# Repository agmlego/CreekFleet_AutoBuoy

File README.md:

# CreekFleet AutoBuoy

Autonomous mark buoys à la [MarkSetBot](https://www.marksetbot.com/), but DIY and (hopefully) lower-cost.

I am not affiliated with nor do I represent the MarkSetBot group. I just thought their concept was neat, but my fleet does not have the capital to buy into it.

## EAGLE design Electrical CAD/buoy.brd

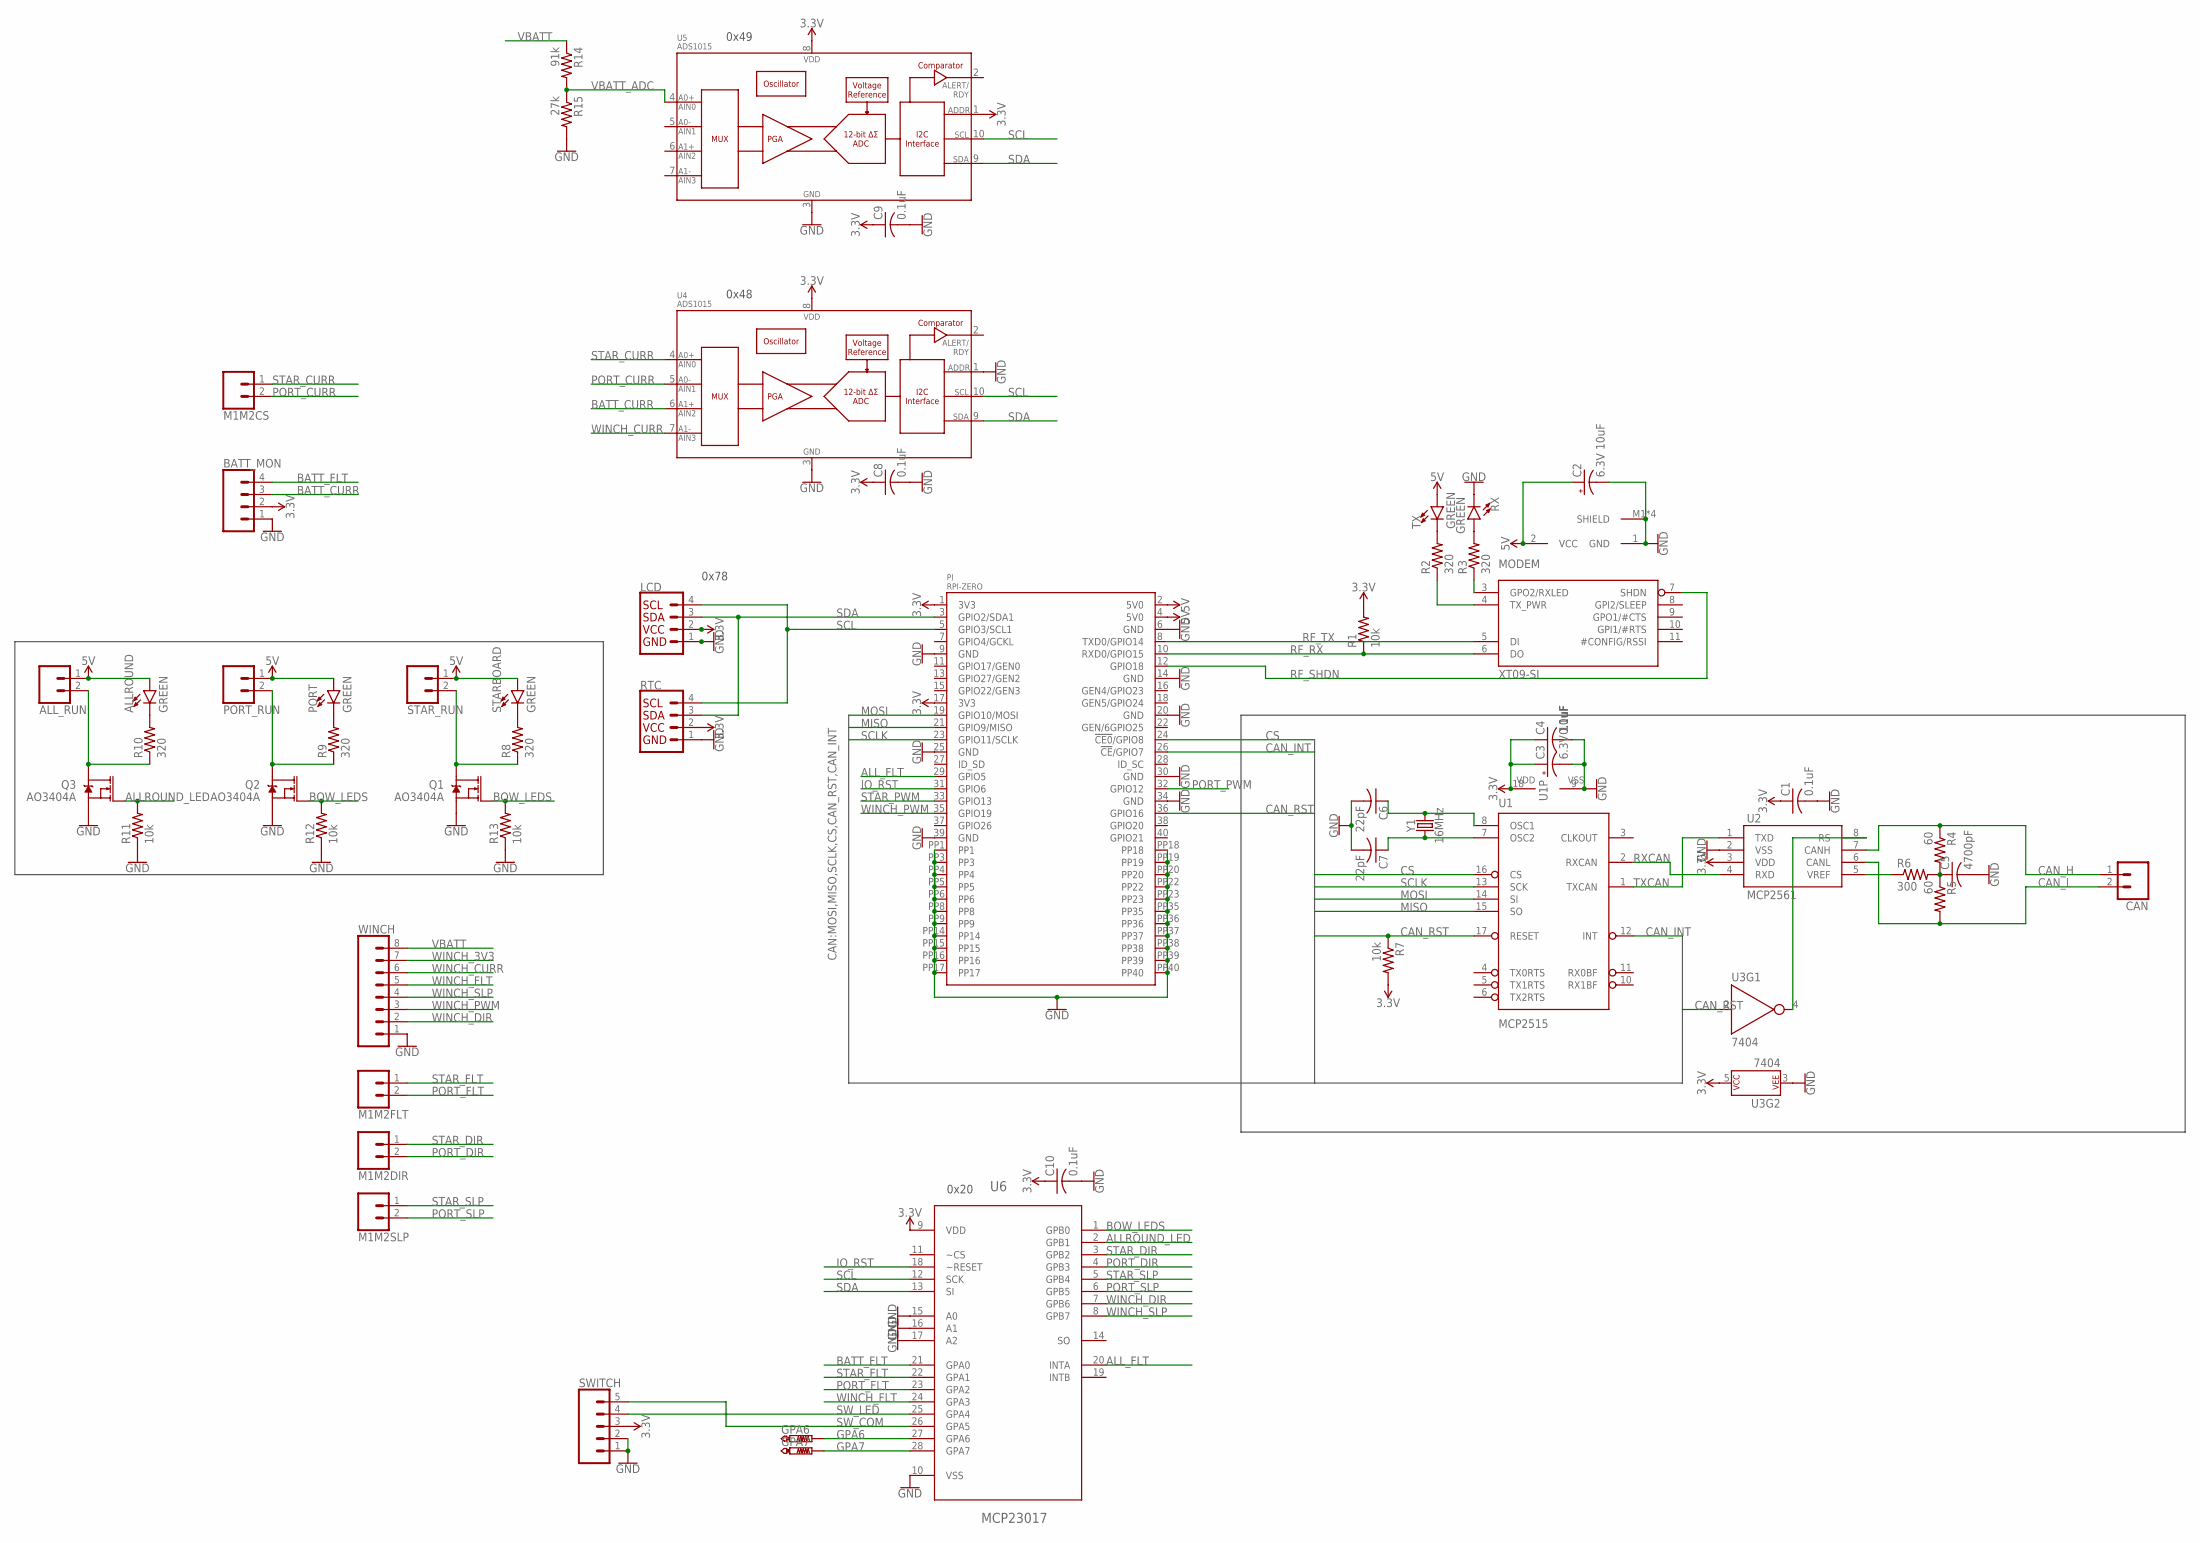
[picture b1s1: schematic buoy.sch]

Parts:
ALLROUND: GREEN; LED-1206
ALL_RUN: CONN_02JST-PTH-2; JST-2-PTH
BATT_MON: CONN_04LOCK; 1X04_LOCK
C1, C4, C8, C9, C10: 0.1uF; C1206
C2, C3: 6.3V 10uF; 153CLV-0405
C5: 4700pF; C1206
C6, C7: 22pF; C1206
CAN: CONN_02JST-PTH-2; JST-2-PTH
GPA6, GPA7: PTR1B1,27; B1,27
LCD: I2C_STANDARD; 1X04
M1M2CS, M1M2DIR, M1M2FLT, M1M2SLP: CONN_02JST-PTH-2; JST-2-PTH
MODEM: XT09-SI
PI: RPI-ZERO; RASP_PI_ZERO_BOARD_FULL
PORT: GREEN; LED-1206
PORT_RUN: CONN_02JST-PTH-2; JST-2-PTH
Q1, Q2, Q3: AO3404A; SOT23-3
R1, R7, R11, R12, R13: 10k; R1206
R2, R3, R8, R9, R10: 320; R1206
R4, R5: 60; R1206
R6: 300; R1206
R14: 91k; R1206
R15: 27k; R1206
RTC: I2C_STANDARD; 1X04
RX: GREEN; LED-1206
STARBOARD: GREEN; LED-1206
STAR_RUN: CONN_02JST-PTH-2; JST-2-PTH
SWITCH: CONN_05LOCK; 1X05_LOCK
TX: GREEN; LED-1206
U1: MCP2515; SO18W
U2: MCP2561; SO08
U3: 7404; SOT353
U4, U5: ADS1015; MSOP10
U6: MCP23017; SOIC127P030X265-28N
WINCH: CONN_08LOCK; 1X08_LOCK
Y1: 16MHz; HC49US

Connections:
3.3V: BATT_MON.2, C1.1, C3.+, C4.1, C8.1, C9.1, C10.1, LCD.2, PI.1 (3V3), PI.17 (3V3), R1.2, R7.2, RTC.2, SWITCH.3, U1.18 (VDD), U2.3 (VDD), U3.5 (P$V+), U4.8 (VDD), U5.1 (ADDR), U5.8 (VDD), U6.9 (VDD)
5V: ALLROUND.A, ALL_RUN.1, C2.+, MODEM.2 (VCC), PI.2 (5V0), PI.4 (5V0), PORT.A, PORT_RUN.1, STARBOARD.A, STAR_RUN.1, TX.A
#CAN_RST: U2.8 (RS), U3.4 (Y)
ALLROUND_IND: ALLROUND.C, R10.2
ALLROUND_LED: Q3.1 (G), R11.2, U6.2 (GPB1)
ALLROUND_LED_LSD: ALL_RUN.2, Q3.3 (D), R10.1
ALL_FLT: PI.29 (GPIO5), U6.20 (INTA)
BATT_CURR: BATT_MON.3, U4.6 (AIN2)
BATT_FLT: BATT_MON.4, U6.21 (GPA0)
BOW_LEDS: Q1.1 (G), Q2.1 (G), R12.2, R13.2, U6.1 (GPB0)
CAN_H: CAN.1, R4.1, U2.7 (CANH)
CAN_INT: PI.26 (!CE!/GPIO7), U1.12 (INT)
CAN_L: CAN.2, R5.2, U2.6 (CANL)
CAN_RST: PI.36 (GPIO16), R7.1, U1.17 (RESET), U3.2 (A)
CAN_TERM: C5.1, R4.2, R5.1, R6.2
CAN_VREF: R6.1, U2.5 (VREF)
CS: PI.24 (!CE0!/GPIO8), U1.16 (CS)
GND: BATT_MON.1, C1.2, C2.-, C3.-, C4.2, C5.2, C6.2, C7.2, C8.2, C9.2, C10.2, LCD.1, MODEM.1 (GND), MODEM.M1 (SHIELD), MODEM.M2 (SHIELD), MODEM.M3 (SHIELD), MODEM.M4 (SHIELD), PI.6 (GND), PI.9 (GND), PI.14 (GND), PI.20 (GND), PI.25 (GND), PI.30 (GND), PI.34 (GND), PI.39 (GND), PI.PP1, PI.PP3, PI.PP4, PI.PP5, PI.PP6, PI.PP8, PI.PP9, PI.PP14, PI.PP15, PI.PP16, PI.PP17, PI.PP18, PI.PP19, PI.PP20, PI.PP22, PI.PP23, PI.PP35, PI.PP36, PI.PP37, PI.PP38, PI.PP39, PI.PP40, Q1.2 (S), Q2.2 (S), Q3.2 (S), R11.1, R12.1, R13.1, R15.2, RTC.1, RX.C, SWITCH.1, SWITCH.2, U1.9 (VSS), U2.2 (VSS), U3.3 (P$V-), U4.1 (ADDR), U4.3 (VSS), U5.3 (VSS), U6.10 (VSS), U6.15 (A0), U6.16 (A1), U6.17 (A2), WINCH.1
GPA6: GPA6.TP, U6.27 (GPA6)
GPA7: GPA7.TP, U6.28 (GPA7)
IO_RST: PI.31 (GPIO6), U6.18 (~RESET)
MISO: PI.21 (GPIO9/MISO), U1.15 (SO)
MOSI: PI.19 (GPIO10/MOSI), U1.14 (SI)
OSC1: C6.1, U1.8 (OSC1), Y1.2
OSC2: C7.1, U1.7 (OSC2), Y1.1
PORT_CURR: M1M2CS.2, U4.5 (AIN1)
PORT_DIR: M1M2DIR.2, U6.4 (GPB3)
PORT_FLT: M1M2FLT.2, U6.23 (GPA2)
PORT_IND: PORT.C, R9.2
PORT_LED_LSD: PORT_RUN.2, Q2.3 (D), R9.1
PORT_PWM: PI.32 (GPIO12)
PORT_SLP: M1M2SLP.2, U6.6 (GPB5)
RF_RX: MODEM.6 (DO), PI.10 (RXD0/GPIO15), R1.1
RF_SHDN: MODEM.7 (SHDN), PI.12 (GPIO18)
RF_TX: MODEM.5 (DI), PI.8 (TXD0/GPIO14)
RXCAN: U1.2 (RXCAN), U2.4 (RXD)
RXLED: MODEM.3 (GPO2/RXLED), R3.1
RXLED_L: R3.2, RX.A
SCL: LCD.4, PI.5 (GPIO3/SCL1), RTC.4, U4.10 (SCL), U5.10 (SCL), U6.12 (SCK)
SCLK: PI.23 (GPIO11/SCLK), U1.13 (SCK)
SDA: LCD.3, PI.3 (GPIO2/SDA1), RTC.3, U4.9 (SDA), U5.9 (SDA), U6.13 (SI)
STARBOARD_LED_LSD: Q1.3 (D), R8.1, STAR_RUN.2
STAR_CURR: M1M2CS.1, U4.4 (AIN0)
STAR_DIR: M1M2DIR.1, U6.3 (GPB2)
STAR_FLT: M1M2FLT.1, U6.22 (GPA1)
STAR_IND: R8.2, STARBOARD.C
STAR_PWM: PI.33 (GPIO13)
STAR_SLP: M1M2SLP.1, U6.5 (GPB4)
SW_COM: SWITCH.5, U6.26 (GPA5)
SW_LED: SWITCH.4, U6.25 (GPA4)
TXCAN: U1.1 (TXCAN), U2.1 (TXD)
TX_PWR: MODEM.4 (TX_PWR), R2.1
TX_PWR_L: R2.2, TX.C
VBATT: R14.1, WINCH.8
VBATT_ADC: R14.2, R15.1, U5.4 (AIN0)
WINCH_3V3: WINCH.7
WINCH_CURR: U4.7 (AIN3), WINCH.6
WINCH_DIR: U6.7 (GPB6), WINCH.2
WINCH_FLT: U6.24 (GPA3), WINCH.5
WINCH_PWM: PI.35 (GPIO19), WINCH.3
WINCH_SLP: U6.8 (GPB7), WINCH.4

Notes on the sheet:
0x78
0x48
0x49
0x20

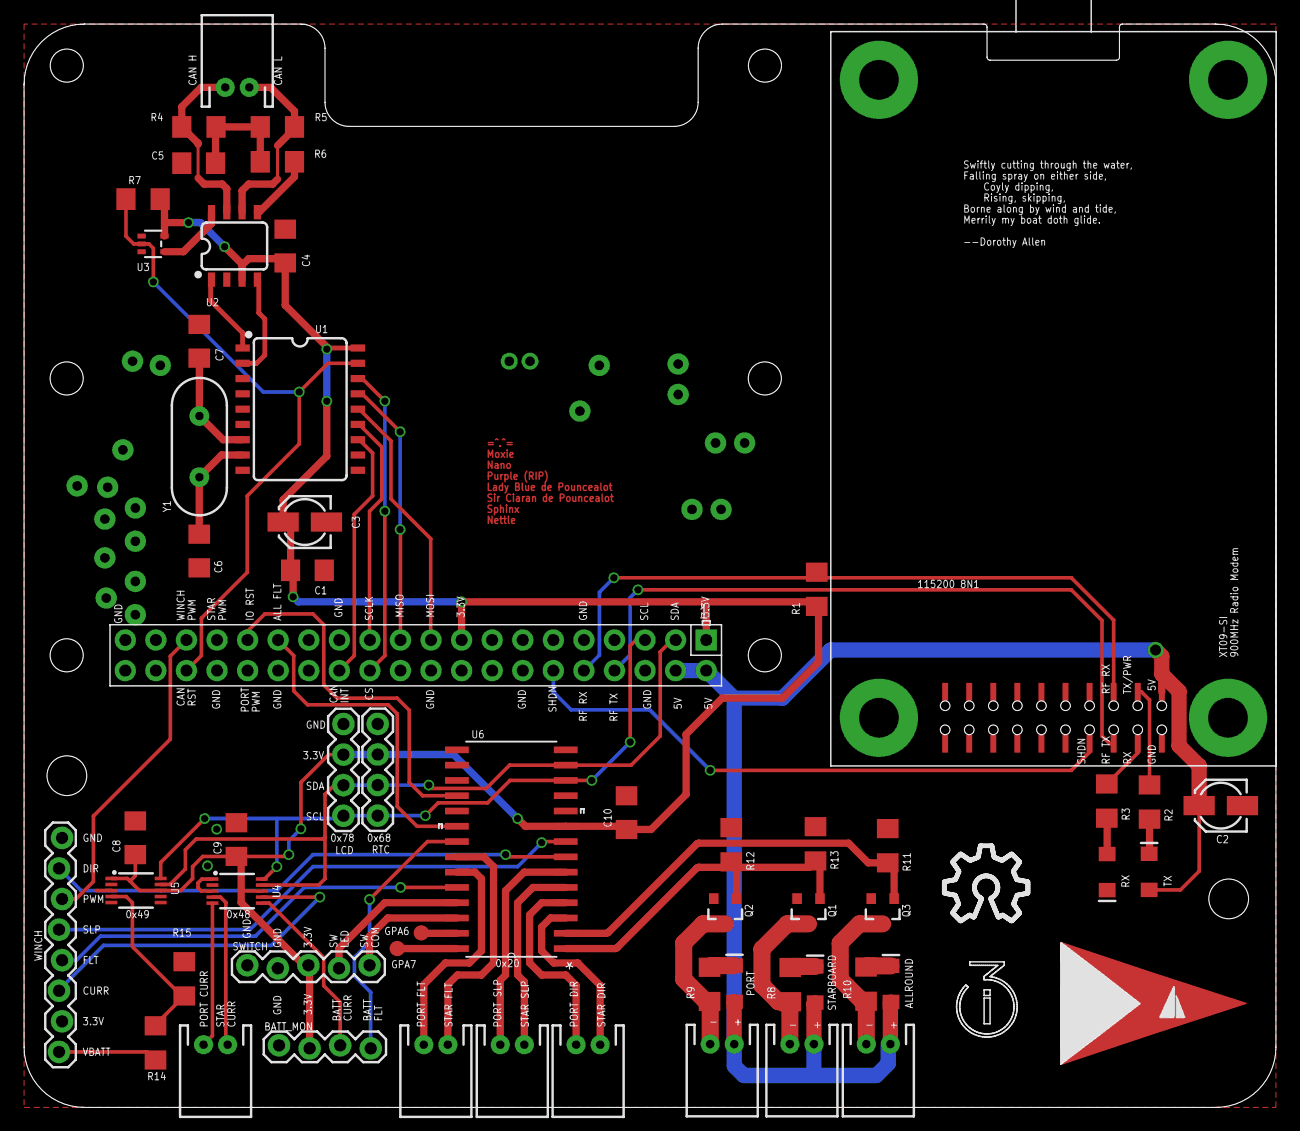
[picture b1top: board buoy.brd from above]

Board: 2 copper layers, 104.0 x 90.0 mm, 60 parts (0 on the bottom side), 58 nets.

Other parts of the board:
U$1: CFLOGO
U$2: I3LOGO
U$3: OSHWLOGO

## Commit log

2020-04-05 Update README.md
    Fleshed out README some to indicate both inspiration and disclaimer.
2020-04-05 Added Inventor and EAGLE files to .gitignore.
2020-04-05 Formatting
2020-04-05 9XTend radio configurations
2020-04-05 Added the geojson files resulting from VSCode GPX extension
2020-04-05 2018 season buoy layout GPX file as a mission target.
2020-04-05 Utility script for range-testing the modems.
    Reads local GPS using GPSD, reads RSSI from modem using pyserial, outputs data on SSD1306 OLED using luma.
    TODO: actually calculate range from remote.
    TODO: Log data to GPX or KML for visualization of range vs RSSI
2020-04-05 ...added pyserial to requirements
2020-04-05 MAVLink-specific 900XTend modem configs
2020-04-05 Design files, including whiteboard sessions
2020-04-05 EAGLE files, beginning of buoy-specific controller
2020-04-05 Mechanical design files, initially created with Autodesk Inventor 2020
2020-04-05 Converted to f-strings, better error diagnostics
2020-04-09 Changing print files from STL to OBJ for better curve representation
2020-04-09 Accidental commit of GCODE, poor form.
2020-04-09 Refactored schematic for I2C IO expander and ADCs.
    This commit in anticipation of offboard current monitoring through motor drivers and current sense board.
2020-04-10 Electrically, schematic and board initial design done.
    Need to lay silk out for component and board ID.
2020-04-10 Completed board art. Pending external review.
2020-04-10 Fixed missing reference issue.
2020-04-10 Added mainboard mount and associated PCBs.
2020-04-10 Added vias to shorten return from C9 to U4.
2020-04-10 Removed Victor SP controllers
2020-04-11 Additional controls components
2020-04-11 Added switch connector.
2020-04-11 FInalized design, sent to OSHPark.
2020-04-11 All primary electronics mounted.
    Moved purchased hardware to dedicated directory.
    FInally got rid of references to outer_drive_right by adding the missing parameter to parameters.xlsx.
2020-04-12 Added control panel.
2020-04-15 Tweaks to design to accomodate material availability.
2020-04-17 Added shore connector, fuse holder, and junction blocks.
2020-04-17 Added power (and CAN) harness.
2020-04-18 Broke winch support mounts in two for ease of manufacture
2020-04-23 Moved printing files to dedicated directory
    CURA project recommended settings
2020-04-23 Figured out support blocker in CURA, reduced printing costs considerably
2020-04-23 Forward endcap GCODE (was on printer)
2020-04-29 Removed since split between hulls works.
2020-04-30 Setting up jigs to manufacture hull mids

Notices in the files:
parts and their libraries:
SparkFun-LED: Licensing: Creative Commons ShareAlike 4.0 International - https://creativecommons.org/licenses/by-sa/4.0
